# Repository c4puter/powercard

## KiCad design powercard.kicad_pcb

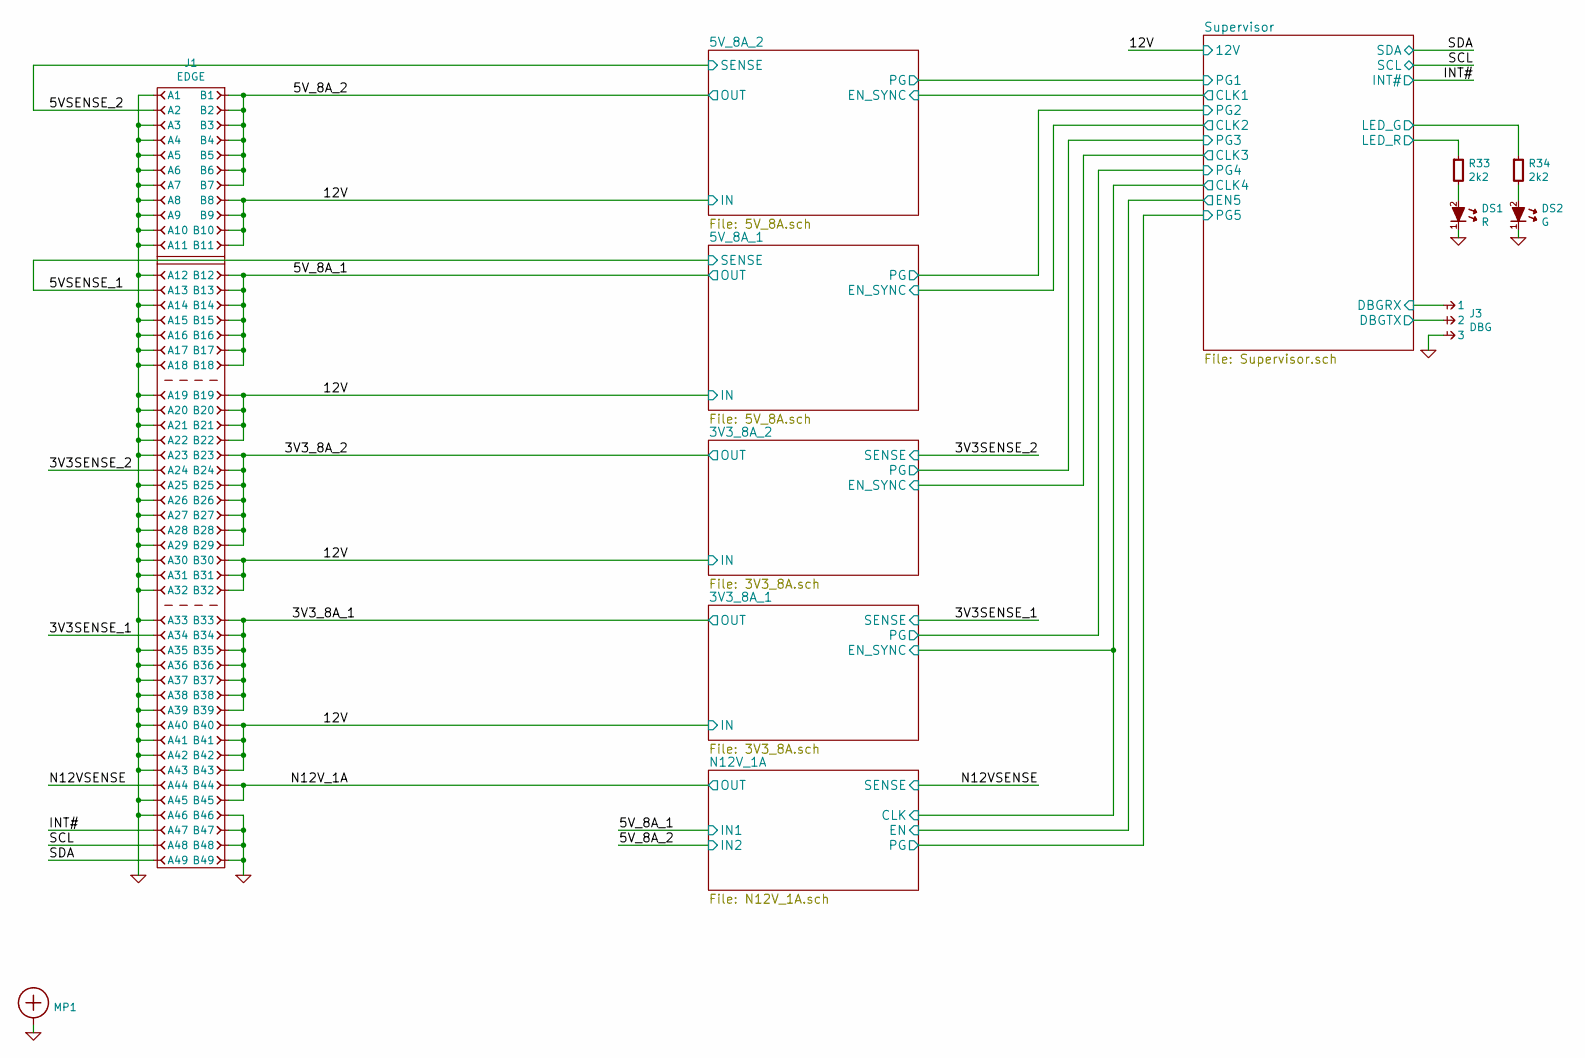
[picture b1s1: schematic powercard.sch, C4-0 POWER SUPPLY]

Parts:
DS1: R; LED-0603
DS2: G; LED-0603
J1: EDGE
J3: DBG; CONN-100MIL-M-1x3
MP1: SCREW; SCREW-3-SUPPORTED
R33, R34: 2k2; RESC1608X50

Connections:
/3V3_8A_1: J1.B33, J1.B34, J1.B35, J1.B36, J1.B37, J1.B38, J1.B39; also elsewhere on the board
/3V3_8A_2: J1.B23, J1.B24, J1.B25, J1.B26, J1.B27, J1.B28, J1.B29; also elsewhere on the board
/5VSENSE_1: J1.A13; also elsewhere on the board
/5V_8A_1: J1.B12, J1.B13, J1.B14, J1.B15, J1.B16, J1.B17, J1.B18; also elsewhere on the board
/5V_8A_2: J1.B1, J1.B2, J1.B3, J1.B4, J1.B5, J1.B6, J1.B7; also elsewhere on the board
/12V: J1.B8, J1.B9, J1.B10, J1.B11, J1.B19, J1.B20, J1.B21, J1.B22, J1.B30, J1.B31, J1.B32, J1.B40, J1.B41, J1.B42, J1.B43; also elsewhere on the board
/INT#: J1.A47; also elsewhere on the board
/N12VSENSE: J1.A44; also elsewhere on the board
/N12V_1A: J1.B44, J1.B45; also elsewhere on the board
/SCL: J1.A48; also elsewhere on the board
/SDA: J1.A49; also elsewhere on the board
/Supervisor/DBGRX: J3.1; also elsewhere on the board
/Supervisor/DBGTX: J3.2; also elsewhere on the board

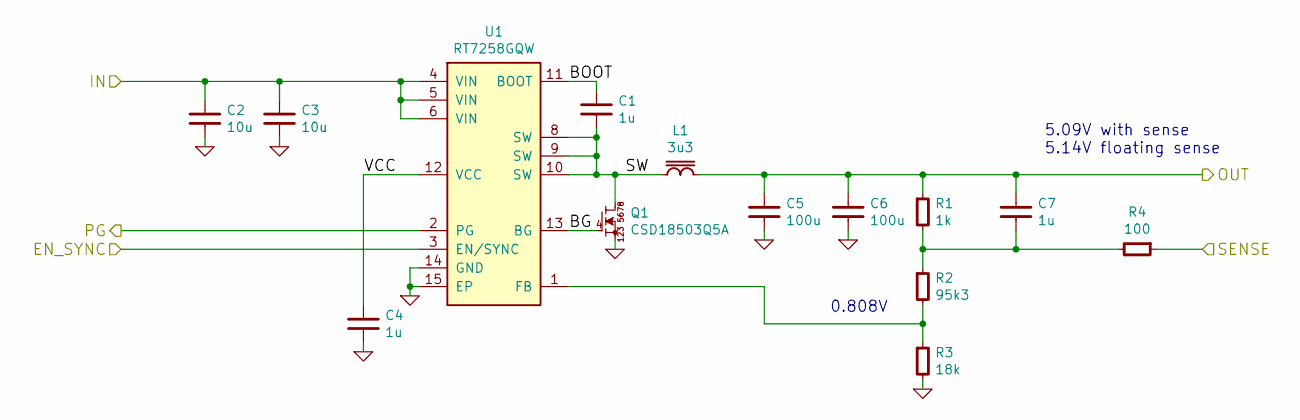
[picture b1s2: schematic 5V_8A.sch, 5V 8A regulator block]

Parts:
C8, C9: 10u; CAPC2012X70
C10, C11, C14: 1u; CAPC1608X55
C12, C13: 100u; CAPC3225X88
L2: 3u3; BOURNS-SRP1238A
Q2: CSD18503Q5A; TEXAS-Q5A
R5: 1k; RESC1608X50
R6: 95k3; RESC1608X50
R7: 18k; RESC1608X50
R8: 100; RESC1608X50
U2: RT7258GQW; DFN50P300X400X80-15

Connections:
/5VSENSE_1: R8.1; also elsewhere on the board
/5V_8A_1: C12.1, C13.1, C14.1, L2.1, R5.1; also elsewhere on the board
/5V_8A_1/BG: Q2.4 (G), U2.13 (BG)
/5V_8A_1/BOOT: C11.1, U2.11 (BOOT)
/5V_8A_1/PG: U2.2 (PG); also elsewhere on the board
/5V_8A_1/SW: C11.2, L2.2, Q2.5 (D), Q2.6 (D), Q2.7 (D), Q2.8 (D), U2.8 (SW), U2.9 (SW), U2.10 (SW)
/5V_8A_1/VCC: C10.1, U2.12 (VCC)
/12V: C8.1, C9.1, U2.4 (VIN), U2.5 (VIN), U2.6 (VIN); also elsewhere on the board
/Supervisor/CLK2: U2.3 (EN/SYNC); also elsewhere on the board
unnamed: C14.2, R5.2, R6.1, R8.2
unnamed: R6.2, R7.1, U2.1 (FB)

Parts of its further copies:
C1, C4, C7: 1u; CAPC1608X55
C2, C3: 10u; CAPC2012X70
C5, C6: 100u; CAPC3225X88
L1: 3u3; BOURNS-SRP1238A
Q1: CSD18503Q5A; TEXAS-Q5A
R1: 1k; RESC1608X50
R2: 95k3; RESC1608X50
R3: 18k; RESC1608X50
R4: 100; RESC1608X50
U1: RT7258GQW; DFN50P300X400X80-15

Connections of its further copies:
/5V_8A_2: C5.1, C6.1, C7.1, L1.1, R1.1; also elsewhere on the board
/5V_8A_2/BG: Q1.4 (G), U1.13 (BG)
/5V_8A_2/BOOT: C1.1, U1.11 (BOOT)
/5V_8A_2/PG: U1.2 (PG); also elsewhere on the board
/5V_8A_2/SW: C1.2, L1.2, Q1.5 (D), Q1.6 (D), Q1.7 (D), Q1.8 (D), U1.8 (SW), U1.9 (SW), U1.10 (SW)
/5V_8A_2/VCC: C4.1, U1.12 (VCC)
/12V: C2.1, C3.1, U1.4 (VIN), U1.5 (VIN), U1.6 (VIN); also elsewhere on the board
/Supervisor/CLK1: U1.3 (EN/SYNC); also elsewhere on the board
unnamed: C7.2, R1.2, R2.1, R4.2
unnamed: R2.2, R3.1, U1.1 (FB)

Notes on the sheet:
0.808V
5.09V with sense 5.14V floating sense

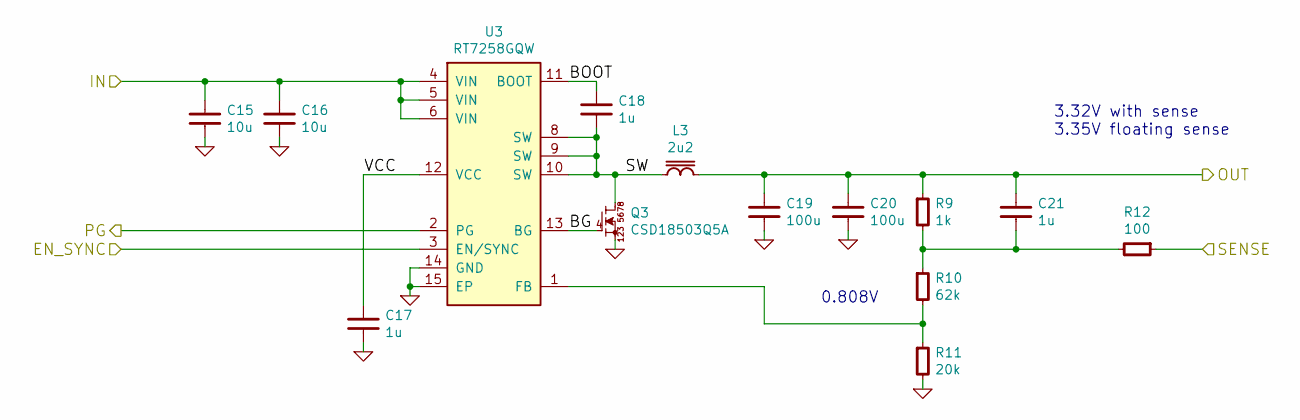
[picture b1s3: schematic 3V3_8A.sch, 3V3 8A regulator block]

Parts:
C15, C16: 10u; CAPC2012X70
C17, C18, C21: 1u; CAPC1608X55
C19, C20: 100u; CAPC3225X88
L3: 2u2; BOURNS-SRP1238A
Q3: CSD18503Q5A; TEXAS-Q5A
R9: 1k; RESC1608X50
R10: 62k; RESC1608X50
R11: 20k; RESC1608X50
R12: 100; RESC1608X50
U3: RT7258GQW; DFN50P300X400X80-15

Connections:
/3V3_8A_1: C19.1, C20.1, C21.1, L3.1, R9.1; also elsewhere on the board
/3V3_8A_1/BG: Q3.4 (G), U3.13 (BG)
/3V3_8A_1/BOOT: C18.1, U3.11 (BOOT)
/3V3_8A_1/PG: U3.2 (PG); also elsewhere on the board
/3V3_8A_1/SW: C18.2, L3.2, Q3.5 (D), Q3.6 (D), Q3.7 (D), Q3.8 (D), U3.8 (SW), U3.9 (SW), U3.10 (SW)
/3V3_8A_1/VCC: C17.1, U3.12 (VCC)
/12V: C15.1, C16.1, U3.4 (VIN), U3.5 (VIN), U3.6 (VIN); also elsewhere on the board
/Supervisor/CLK4: U3.3 (EN/SYNC); also elsewhere on the board
unnamed: C21.2, R9.2, R10.1, R12.2
unnamed: R10.2, R11.1, U3.1 (FB)

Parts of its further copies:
C22, C23: 10u; CAPC2012X70
C24, C25, C28: 1u; CAPC1608X55
C26, C27: 100u; CAPC3225X88
L4: 2u2; BOURNS-SRP1238A
Q4: CSD18503Q5A; TEXAS-Q5A
R13: 1k; RESC1608X50
R14: 62k; RESC1608X50
R15: 20k; RESC1608X50
R16: 100; RESC1608X50
U4: RT7258GQW; DFN50P300X400X80-15

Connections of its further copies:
/3V3_8A_2: C26.1, C27.1, C28.1, L4.1, R13.1; also elsewhere on the board
/3V3_8A_2/BG: Q4.4 (G), U4.13 (BG)
/3V3_8A_2/BOOT: C25.1, U4.11 (BOOT)
/3V3_8A_2/PG: U4.2 (PG); also elsewhere on the board
/3V3_8A_2/SW: C25.2, L4.2, Q4.5 (D), Q4.6 (D), Q4.7 (D), Q4.8 (D), U4.8 (SW), U4.9 (SW), U4.10 (SW)
/3V3_8A_2/VCC: C24.1, U4.12 (VCC)
/12V: C22.1, C23.1, U4.4 (VIN), U4.5 (VIN), U4.6 (VIN); also elsewhere on the board
/N12V_1A/CLK: U4.3 (EN/SYNC); also elsewhere on the board
unnamed: C28.2, R13.2, R14.1, R16.2
unnamed: R14.2, R15.1, U4.1 (FB)

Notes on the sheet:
3.32V with sense 3.35V floating sense
0.808V

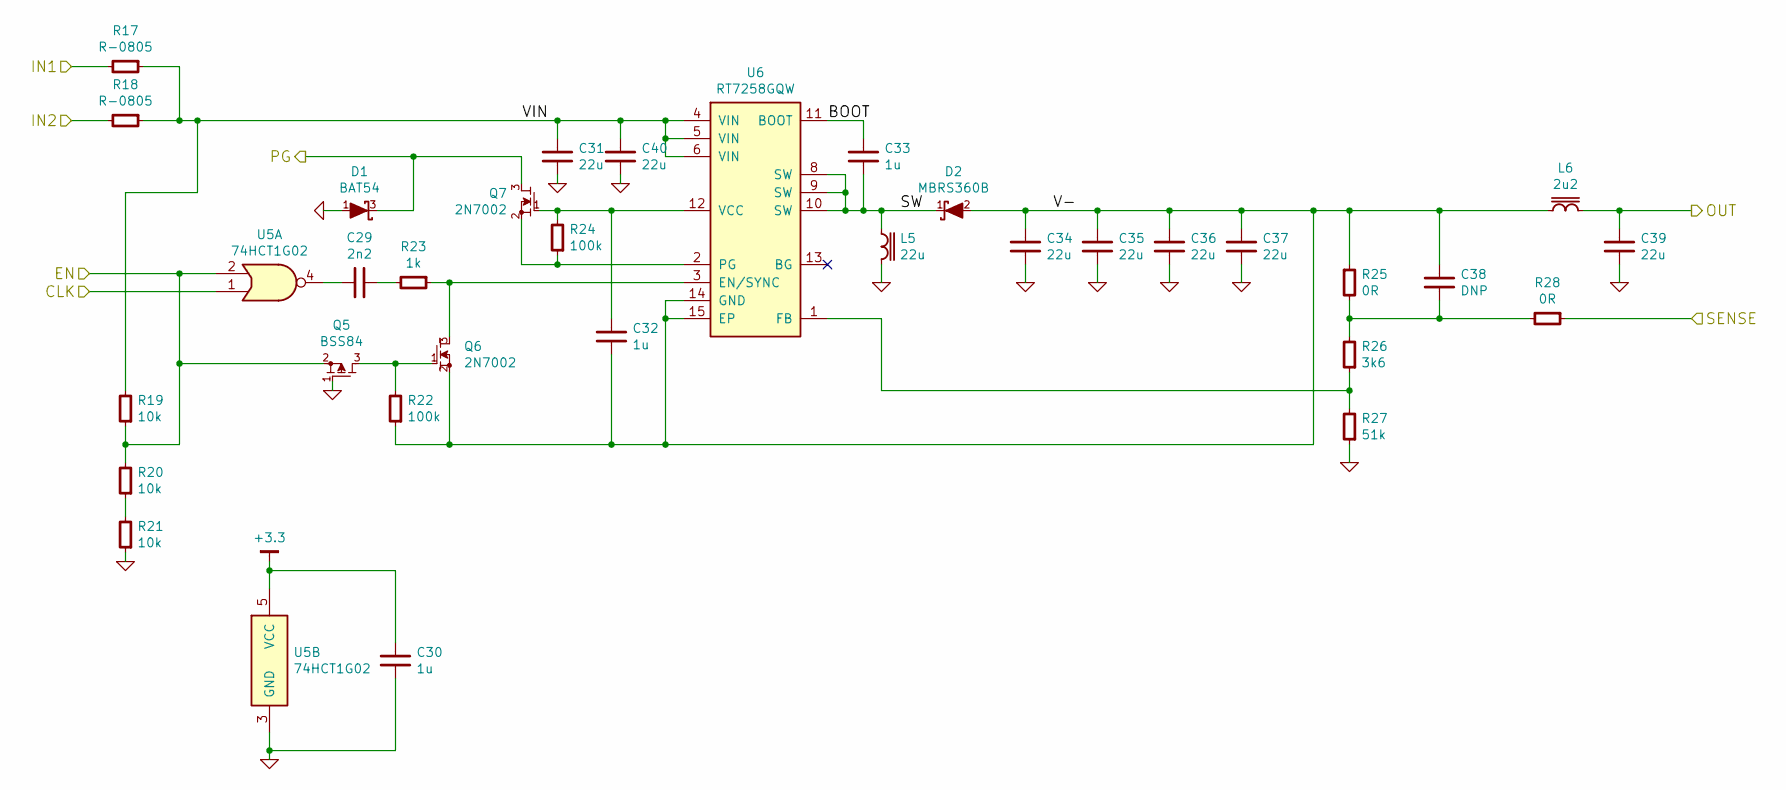
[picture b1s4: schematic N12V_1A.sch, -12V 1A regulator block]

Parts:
C29: 2n2; CAPC1608X55
C30, C32, C33: 1u; CAPC1608X55
C31, C34, C35, C36, C37, C39, C40: 22u; CAPC3216X70
C38: DNP; CAPC1608X55
D1: BAT54; SOT-23
D2: MBRS360B; DIOM5436X244
L5: 22u; BOURNS-SRR1210
L6: 2u2; INDC2520X220
Q5: BSS84; SOT-23
Q6, Q7: 2N7002; SOT-23
R17, R18: R-0805; RESC2012X50
R19, R20, R21: 10k; RESC1608X50
R22, R24: 100k; RESC1608X50
R23: 1k; RESC1608X50
R25, R28: 0R; RESC1608X50
R26: 3k6; RESC1608X50
R27: 51k; RESC1608X50
U5: 74HCT1G02; SC-70-5
U6: RT7258GQW; DFN50P300X400X80-15

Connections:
+3.3: C30.1, U5.5 (VCC); also elsewhere on the board
/5V_8A_1: R17.2; also elsewhere on the board
/5V_8A_2: R18.2; also elsewhere on the board
/N12VSENSE: R28.1; also elsewhere on the board
/N12V_1A: C39.1, L6.1; also elsewhere on the board
/N12V_1A/BOOT: C33.1, U6.11 (BOOT)
/N12V_1A/CLK: U5.1; also elsewhere on the board
/N12V_1A/EN: Q5.2 (S), R19.1, R20.2, U5.2; also elsewhere on the board
/N12V_1A/PG: D1.3 (K), Q7.3; also elsewhere on the board
/N12V_1A/SW: C33.2, D2.1 (K), L5.2, U6.8 (SW), U6.9 (SW), U6.10 (SW)
/N12V_1A/V-: C32.2, C34.1, C35.1, C36.1, C37.1, C38.1, D2.2 (A), L6.2, Q6.2, R22.1, R25.1, U6.14 (GND), U6.15 (EP)
/N12V_1A/VIN: C31.1, C40.1, R17.1, R18.1, R19.2, U6.4 (VIN), U6.5 (VIN), U6.6 (VIN)
unnamed: C29.1, R23.2
unnamed: C29.2, U5.4
unnamed: C32.1, Q7.1, R24.2, U6.12 (VCC)
unnamed: C38.2, R25.2, R26.2, R28.2
unnamed: Q5.3 (D), Q6.1, R22.2
unnamed: Q6.3, R23.1, U6.3 (EN/SYNC)
unnamed: R20.1, R21.2
unnamed: R26.1, R27.2, U6.1 (FB)

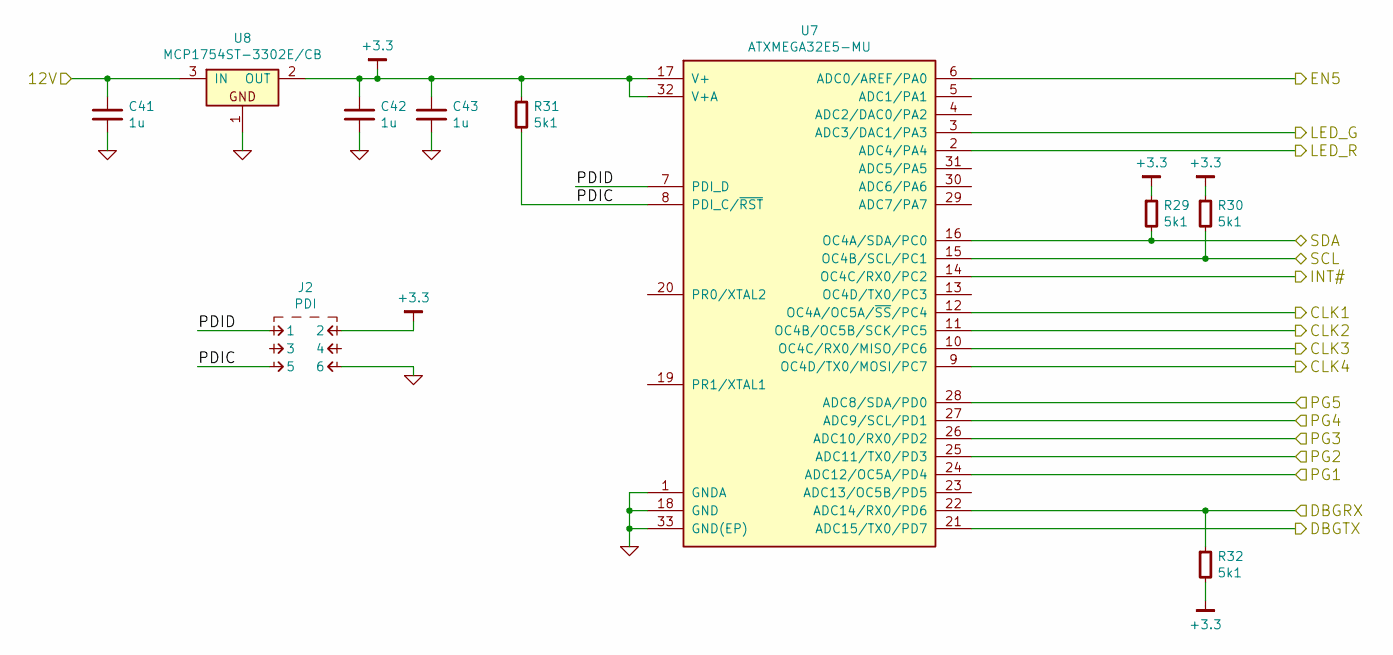
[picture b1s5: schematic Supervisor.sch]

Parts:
C41, C42, C43: 1u; CAPC1608X55
J2: PDI; CONN-100MIL-M-2x3
R29, R30, R31, R32: 5k1; RESC1608X50
U7: ATXMEGA32E5-MU; QFN50P500X500X100-33
U8: MCP1754ST-3302E/CB; SOT-23

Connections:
+3.3: C42.1, C43.1, J2.2, R29.1, R30.1, R31.1, R32.2, U7.17 (V+), U7.32 (V+A), U8.2 (OUT); also elsewhere on the board
/3V3_8A_1/PG: U7.26 (ADC10/RX0/PD2); also elsewhere on the board
/3V3_8A_2/PG: U7.27 (ADC9/SCL/PD1); also elsewhere on the board
/5V_8A_1/PG: U7.24 (ADC12/OC5A/PD4); also elsewhere on the board
/5V_8A_2/PG: U7.25 (ADC11/TX0/PD3); also elsewhere on the board
/12V: C41.1, U8.3 (IN); also elsewhere on the board
/INT#: U7.14 (OC4C/RX0/PC2); also elsewhere on the board
/N12V_1A/CLK: U7.9 (OC4D/TX0/MOSI/PC7); also elsewhere on the board
/N12V_1A/EN: U7.6 (ADC0/AREF/PA0); also elsewhere on the board
/N12V_1A/PG: U7.28 (ADC8/SDA/PD0); also elsewhere on the board
/SCL: R30.2, U7.15 (OC4B/SCL/PC1); also elsewhere on the board
/SDA: R29.2, U7.16 (OC4A/SDA/PC0); also elsewhere on the board
/Supervisor/CLK1: U7.11 (OC4B/OC5B/SCK/PC5); also elsewhere on the board
/Supervisor/CLK2: U7.12 (OC4A/OC5A/~SS~/PC4); also elsewhere on the board
/Supervisor/CLK4: U7.10 (OC4C/RX0/MISO/PC6); also elsewhere on the board
/Supervisor/DBGRX: R32.1, U7.22 (ADC14/RX0/PD6); also elsewhere on the board
/Supervisor/DBGTX: U7.21 (ADC15/TX0/PD7); also elsewhere on the board
/Supervisor/LED_C: U7.3 (ADC3/DAC1/PA3); also elsewhere on the board
/Supervisor/PDIC: J2.5, R31.2, U7.8 (PDI_C/~RST)
/Supervisor/PDID: J2.1, U7.7 (PDI_D)

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
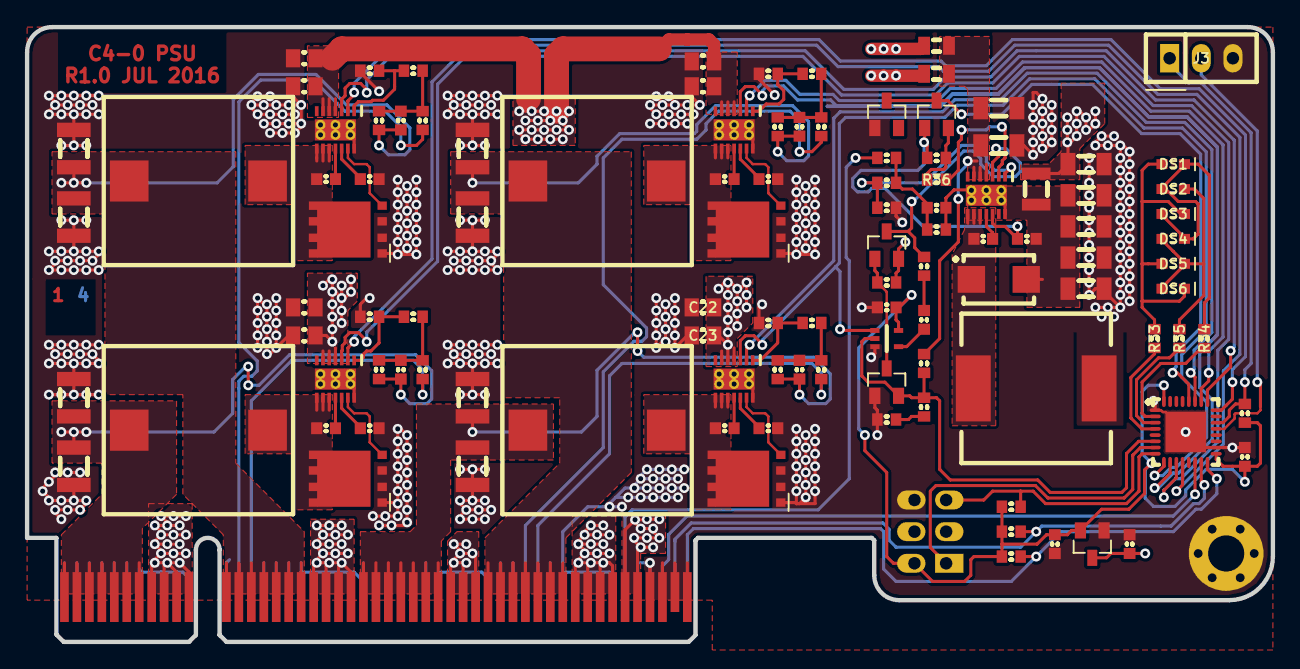
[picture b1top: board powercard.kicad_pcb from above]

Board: 4 copper layers, 100.0 x 49.4 mm, 112 parts (0 on the bottom side), 74 nets.

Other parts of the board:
DS3: 3VA; LED-0603
DS4: 3VB; LED-0603
DS5: N12; LED-0603
DS6: SFY; LED-0603
R35: 1k; RESC1608X50
R36: 5k1; RESC1608X50

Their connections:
/Supervisor/LED_C: R35.2; also elsewhere on the board

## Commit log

2016-07-01 Layout tweaks
2016-07-01 More PCB tweaks
2016-07-02 Even more PCB tweaks
2016-07-03 Commit R1.0 sent to fab
2016-07-15 Final rev take 2
